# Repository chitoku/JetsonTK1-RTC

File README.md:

# JetsonTK1-RTC
RTC module for Jetson TK1

# What this is

This module is to give a battery backup RTC functionality to Jetson TK1, aside other minor features.

## RTC

The main feature of this board is to give a battery backup RTC functionality to Jetson TK1.
The module is designed to be placed on the J3A1 (2x25) expansion header of Jetson TK1 and is designed to be used with Santyago's Grinch Custom Kernel.
The RTC fuctionality was verifid on the initial revision of the assembled board and was cofirmed to be working in the way written  [here](http://elinux.org/Jetson/RTC). 

## Grove connectors

The board also has two Grove I2C connectors, intended to accomodate 3.3V I2C Grove modules, however they are not yet tested.
For Grove system, please refere [here](http://www.seeedstudio.com/wiki/Grove_System).

## Barometer sensor

Supplementary, the board is intended to give an accesss to MPL115A2 barometer sensor, but this sensor does not work on the initial revision of the assembled board. (See "Attention" section)

# Attribute

The design of the circuit and the basic setup is based on Santyago's [this](https://devtalk.nvidia.com/default/topic/769727/embedded-systems/-howto-battery-backup-rtc/) Hot-To.
The Grinch Custom Kernel is a work of [Santyago](https://devtalk.nvidia.com/member/1982212/).

# Attention!

The barometic sensor, MPL115A2 did not work on the initial revision of the assembled board.
It is later found that the pull-up on RST/CS pin (pin5) is mssing, so this is suspected to be the cause. 
More investigation and a fix is desired.

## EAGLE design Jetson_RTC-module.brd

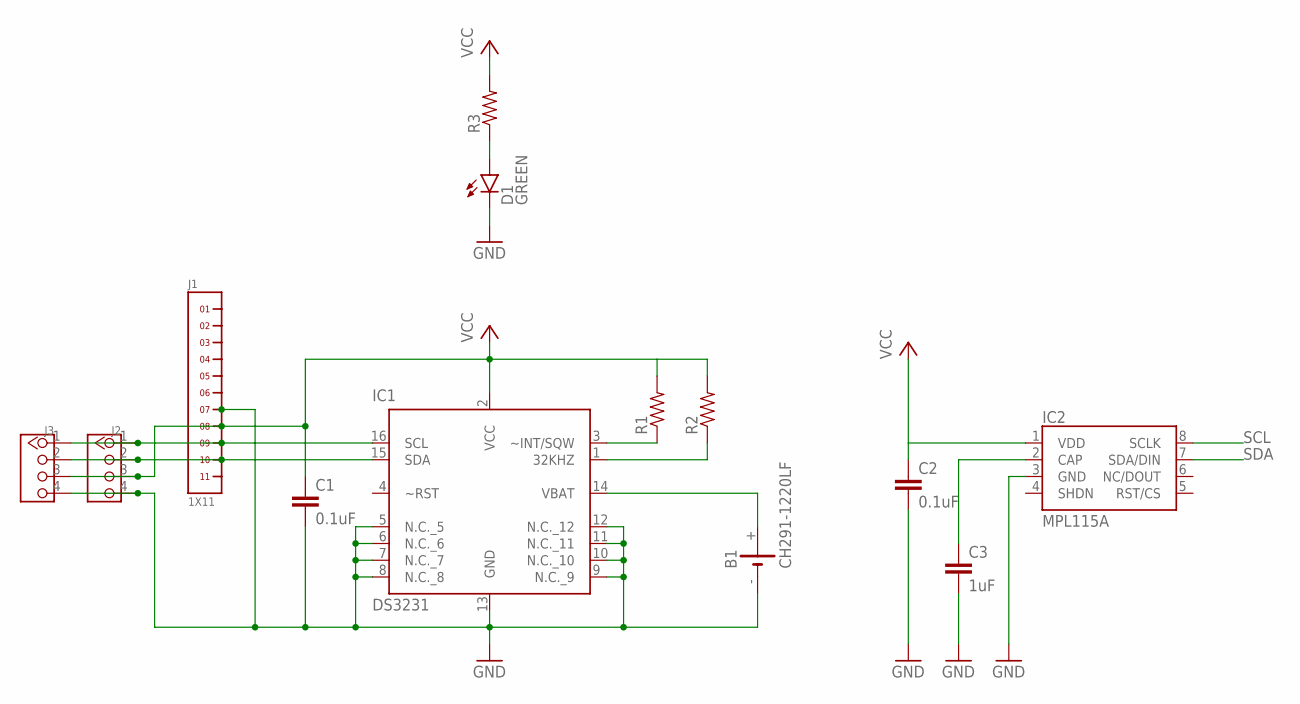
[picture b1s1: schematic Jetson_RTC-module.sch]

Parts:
B1: CH291-1220LF
C1, C2: 0.1uF; C1608
C3: 1uF; C1608
D1: GREEN; LED-0603
IC1: DS3231; SO16L
IC2: MPL115A; LGA8
J1: 1X11
J2, J3: TWIG-4P-2.0-2.0; 4P-2.0
R1, R2, R3: RESISTOR0603; 0603-RES

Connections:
GND: B1.-, C1.2, C2.2, C3.2, D1.C, IC1.5 (N.C._5), IC1.6 (N.C._6), IC1.7 (N.C._7), IC1.8 (N.C._8), IC1.9 (N.C._9), IC1.10 (N.C._10), IC1.11 (N.C._11), IC1.12 (N.C._12), IC1.13 (GND), IC2.3 (GND), J1.7, J2.4, J3.4
unnamed: B1.+, IC1.14 (VBAT)
unnamed: IC1.1 (32KHZ), R2.1
unnamed: IC1.3 (~INT/SQW), R1.1
unnamed: C3.1, IC2.2 (CAP)
unnamed: D1.A, R3.1
SCL: IC1.16 (SCL), IC2.8 (SCLK), J1.9, J2.1, J3.1
SDA: IC1.15 (SDA), IC2.7 (SDA/DIN), J1.10, J2.2, J3.2
VCC: C1.1, C2.1, IC1.2 (VCC), IC2.1 (VDD), J1.8, J2.3, J3.3, R1.2, R2.2, R3.2

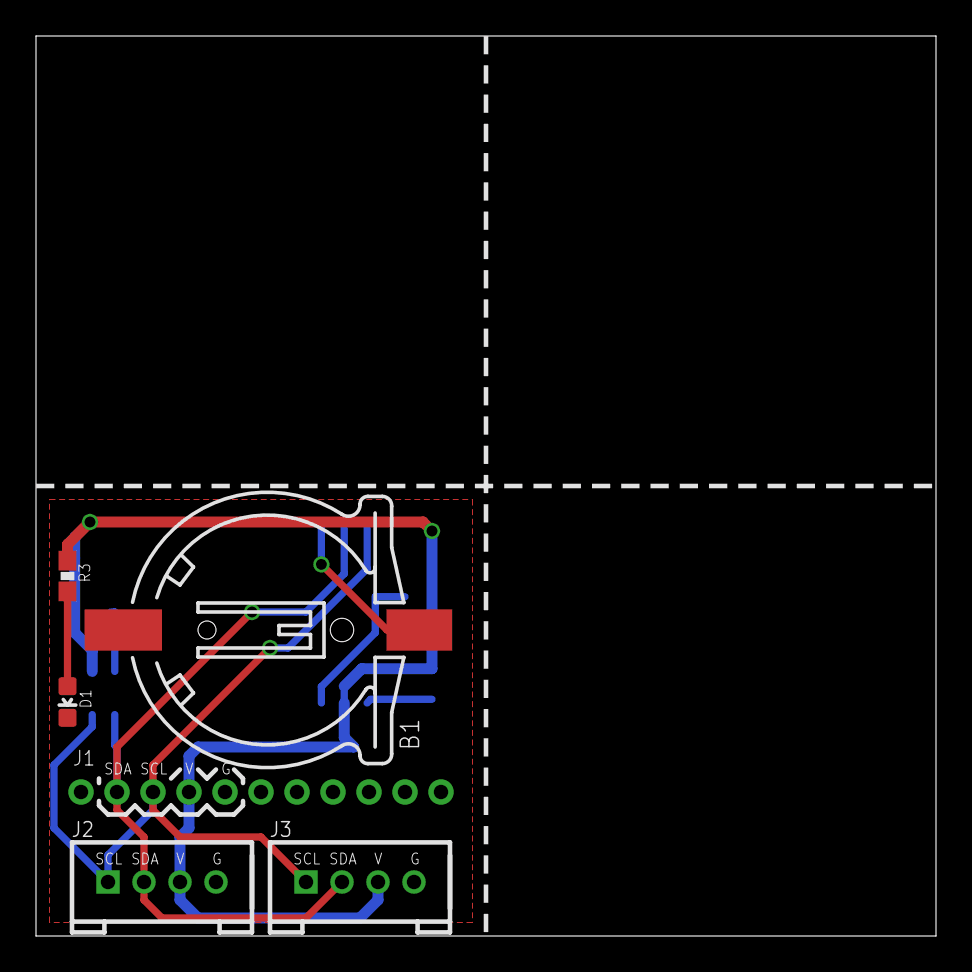
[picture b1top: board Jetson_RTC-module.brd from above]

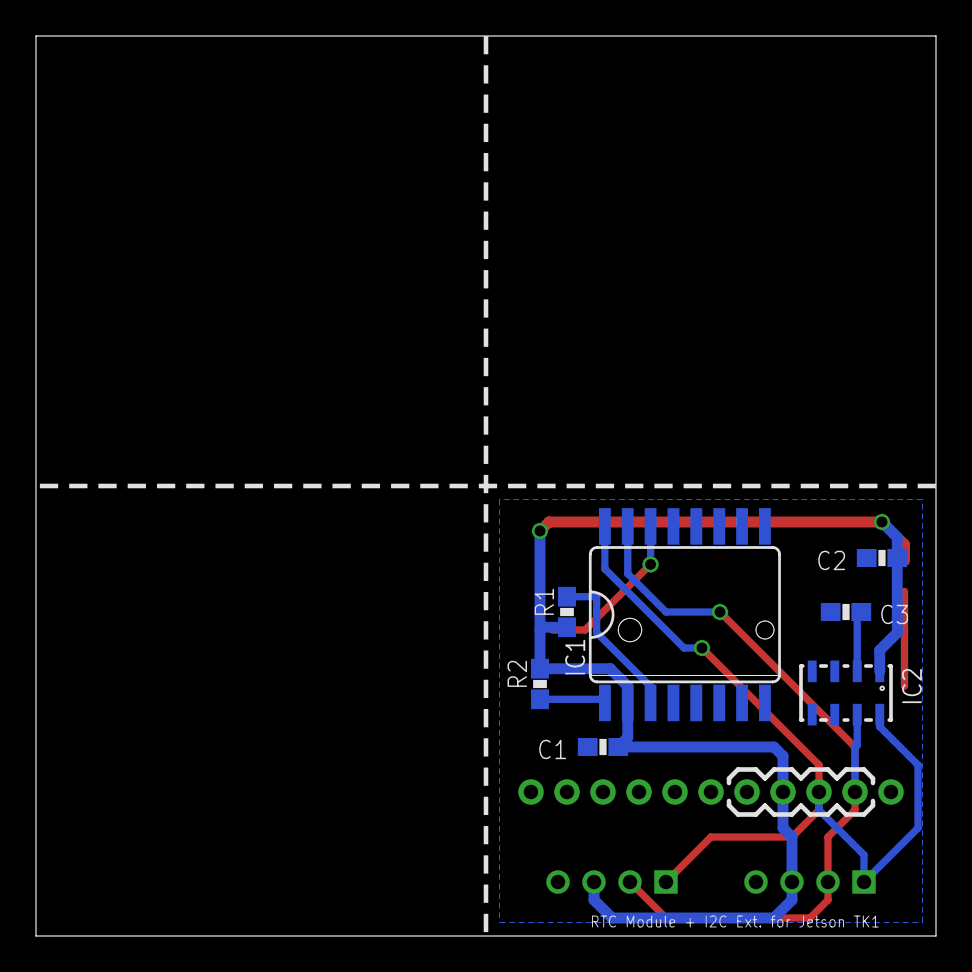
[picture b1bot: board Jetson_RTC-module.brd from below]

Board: 2 copper layers, 50.0 x 50.0 mm, 13 parts (8 on the bottom side), 9 nets.

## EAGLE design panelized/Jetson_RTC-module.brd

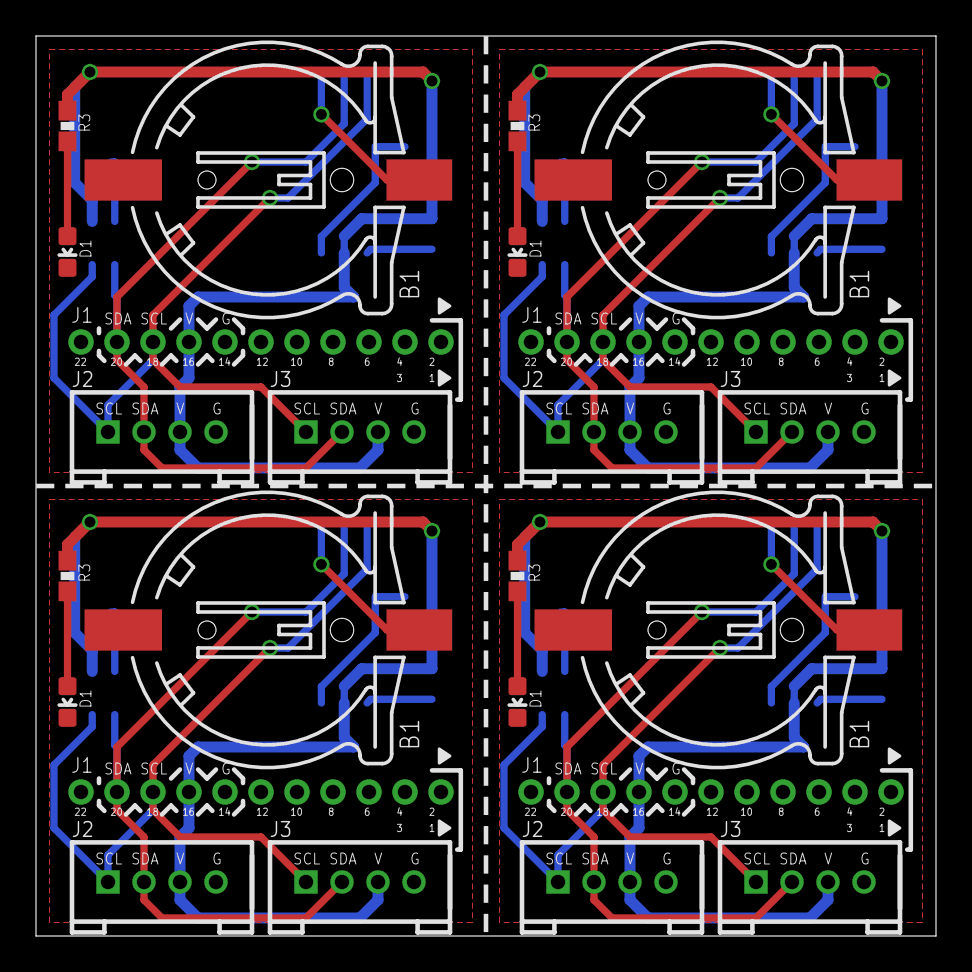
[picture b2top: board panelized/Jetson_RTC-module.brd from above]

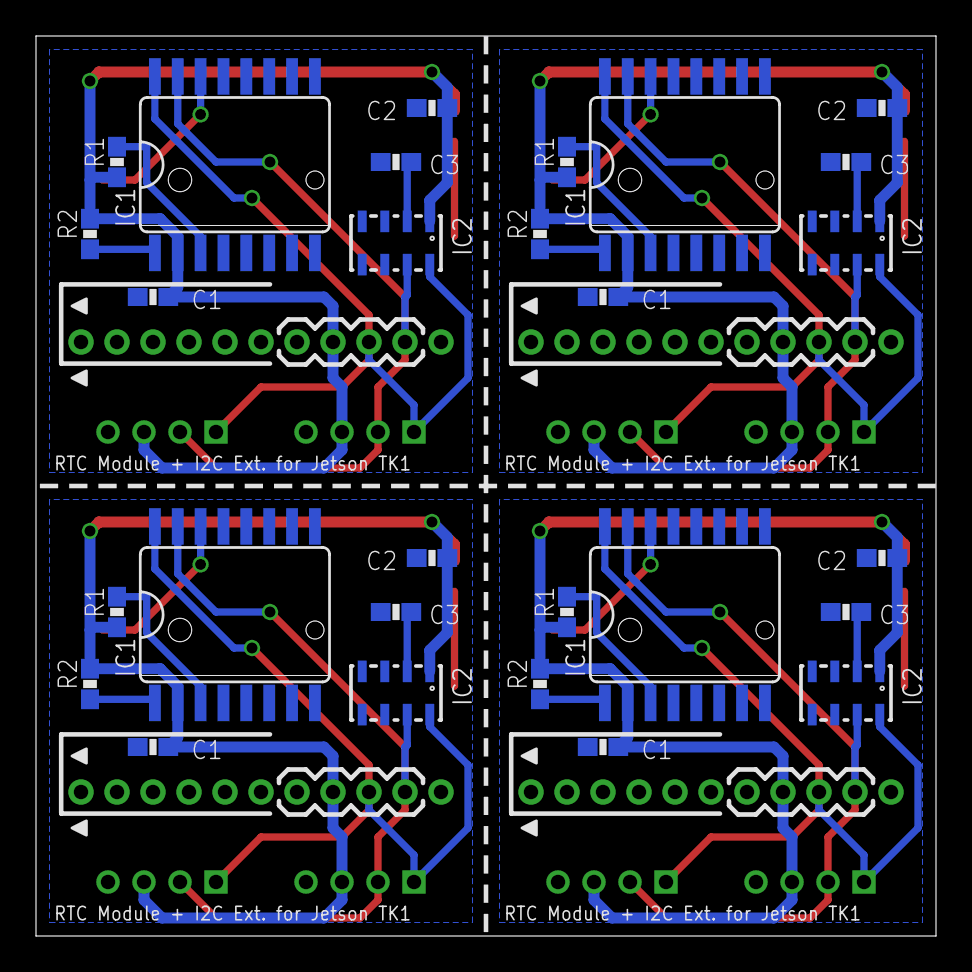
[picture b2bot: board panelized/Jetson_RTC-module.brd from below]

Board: 2 copper layers, 50.0 x 50.0 mm, 52 parts (32 on the bottom side), 36 nets.

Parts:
B1, B2, B3, B4: CH291-1220LF
C1, C2, C4, C5, C7, C8, C10, C11: 0.1uF; C1608
C3, C6, C9, C12: 1uF; C1608
D1, D2, D3, D4: GREEN; LED-0603
IC1, IC3, IC5, IC7: DS3231; SO16L
IC2, IC4, IC6, IC8: MPL115A; LGA8
J1, J5, J8, J11: 1X11
J2, J3, J4, J6, J7, J9, J10, J12: 4P-2.0
R1, R2, R3, R4, R5, R6, R7, R8, R9, R10, R11, R12: 0603-RES

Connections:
GND: B1.-, C1.2, C2.2, C3.2, D1.C, IC1.5, IC1.6, IC1.7, IC1.8, IC1.9, IC1.10, IC1.11, IC1.12, IC1.13, IC2.3, J1.7, J2.4, J3.4
GND1: B2.-, C4.2, C5.2, C6.2, D2.C, IC3.5, IC3.6, IC3.7, IC3.8, IC3.9, IC3.10, IC3.11, IC3.12, IC3.13, IC4.3, J4.4, J5.7, J6.4
GND2: B3.-, C7.2, C8.2, C9.2, D3.C, IC5.5, IC5.6, IC5.7, IC5.8, IC5.9, IC5.10, IC5.11, IC5.12, IC5.13, IC6.3, J7.4, J8.7, J9.4
GND3: B4.-, C10.2, C11.2, C12.2, D4.C, IC7.5, IC7.6, IC7.7, IC7.8, IC7.9, IC7.10, IC7.11, IC7.12, IC7.13, IC8.3, J10.4, J11.7, J12.4
unnamed: B1.+, IC1.14
unnamed: IC1.1, R2.1
unnamed: IC1.3, R1.1
unnamed: C3.1, IC2.2
unnamed: D1.A, R3.1
unnamed: B2.+, IC3.14
unnamed: IC3.1, R5.1
unnamed: IC3.3, R4.1
unnamed: C6.1, IC4.2
unnamed: D2.A, R6.1
unnamed: B3.+, IC5.14
unnamed: IC5.1, R8.1
unnamed: IC5.3, R7.1
unnamed: C9.1, IC6.2
unnamed: D3.A, R9.1
unnamed: B4.+, IC7.14
unnamed: IC7.1, R11.1
unnamed: IC7.3, R10.1
unnamed: C12.1, IC8.2
unnamed: D4.A, R12.1
SCL: IC1.16, IC2.8, J1.9, J2.1, J3.1
SCL1: IC3.16, IC4.8, J4.1, J5.9, J6.1
SCL2: IC5.16, IC6.8, J7.1, J8.9, J9.1
SCL3: IC7.16, IC8.8, J10.1, J11.9, J12.1
SDA: IC1.15, IC2.7, J1.10, J2.2, J3.2
SDA1: IC3.15, IC4.7, J4.2, J5.10, J6.2
SDA2: IC5.15, IC6.7, J7.2, J8.10, J9.2
SDA3: IC7.15, IC8.7, J10.2, J11.10, J12.2
VCC: C1.1, C2.1, IC1.2, IC2.1, J1.8, J2.3, J3.3, R1.2, R2.2, R3.2
VCC1: C4.1, C5.1, IC3.2, IC4.1, J4.3, J5.8, J6.3, R4.2, R5.2, R6.2
VCC2: C7.1, C8.1, IC5.2, IC6.1, J7.3, J8.8, J9.3, R7.2, R8.2, R9.2
VCC3: C10.1, C11.1, IC7.2, IC8.1, J10.3, J11.8, J12.3, R10.2, R11.2, R12.2

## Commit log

2016-01-25 Initial
2016-01-25 Update README.md
    Fill the content.
2016-01-29 Images uploaded

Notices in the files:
parts and their libraries:
SparkFun-Sensors: Licensing: Creative Commons ShareAlike 4.0 International - https://creativecommons.org/licenses/by-sa/4.0
